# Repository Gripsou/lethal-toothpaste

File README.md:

README
======

BRIEF
-----

This is the repository for STM32 sockets.

NOTE :
------

This text is in _Work in Progress_ state.

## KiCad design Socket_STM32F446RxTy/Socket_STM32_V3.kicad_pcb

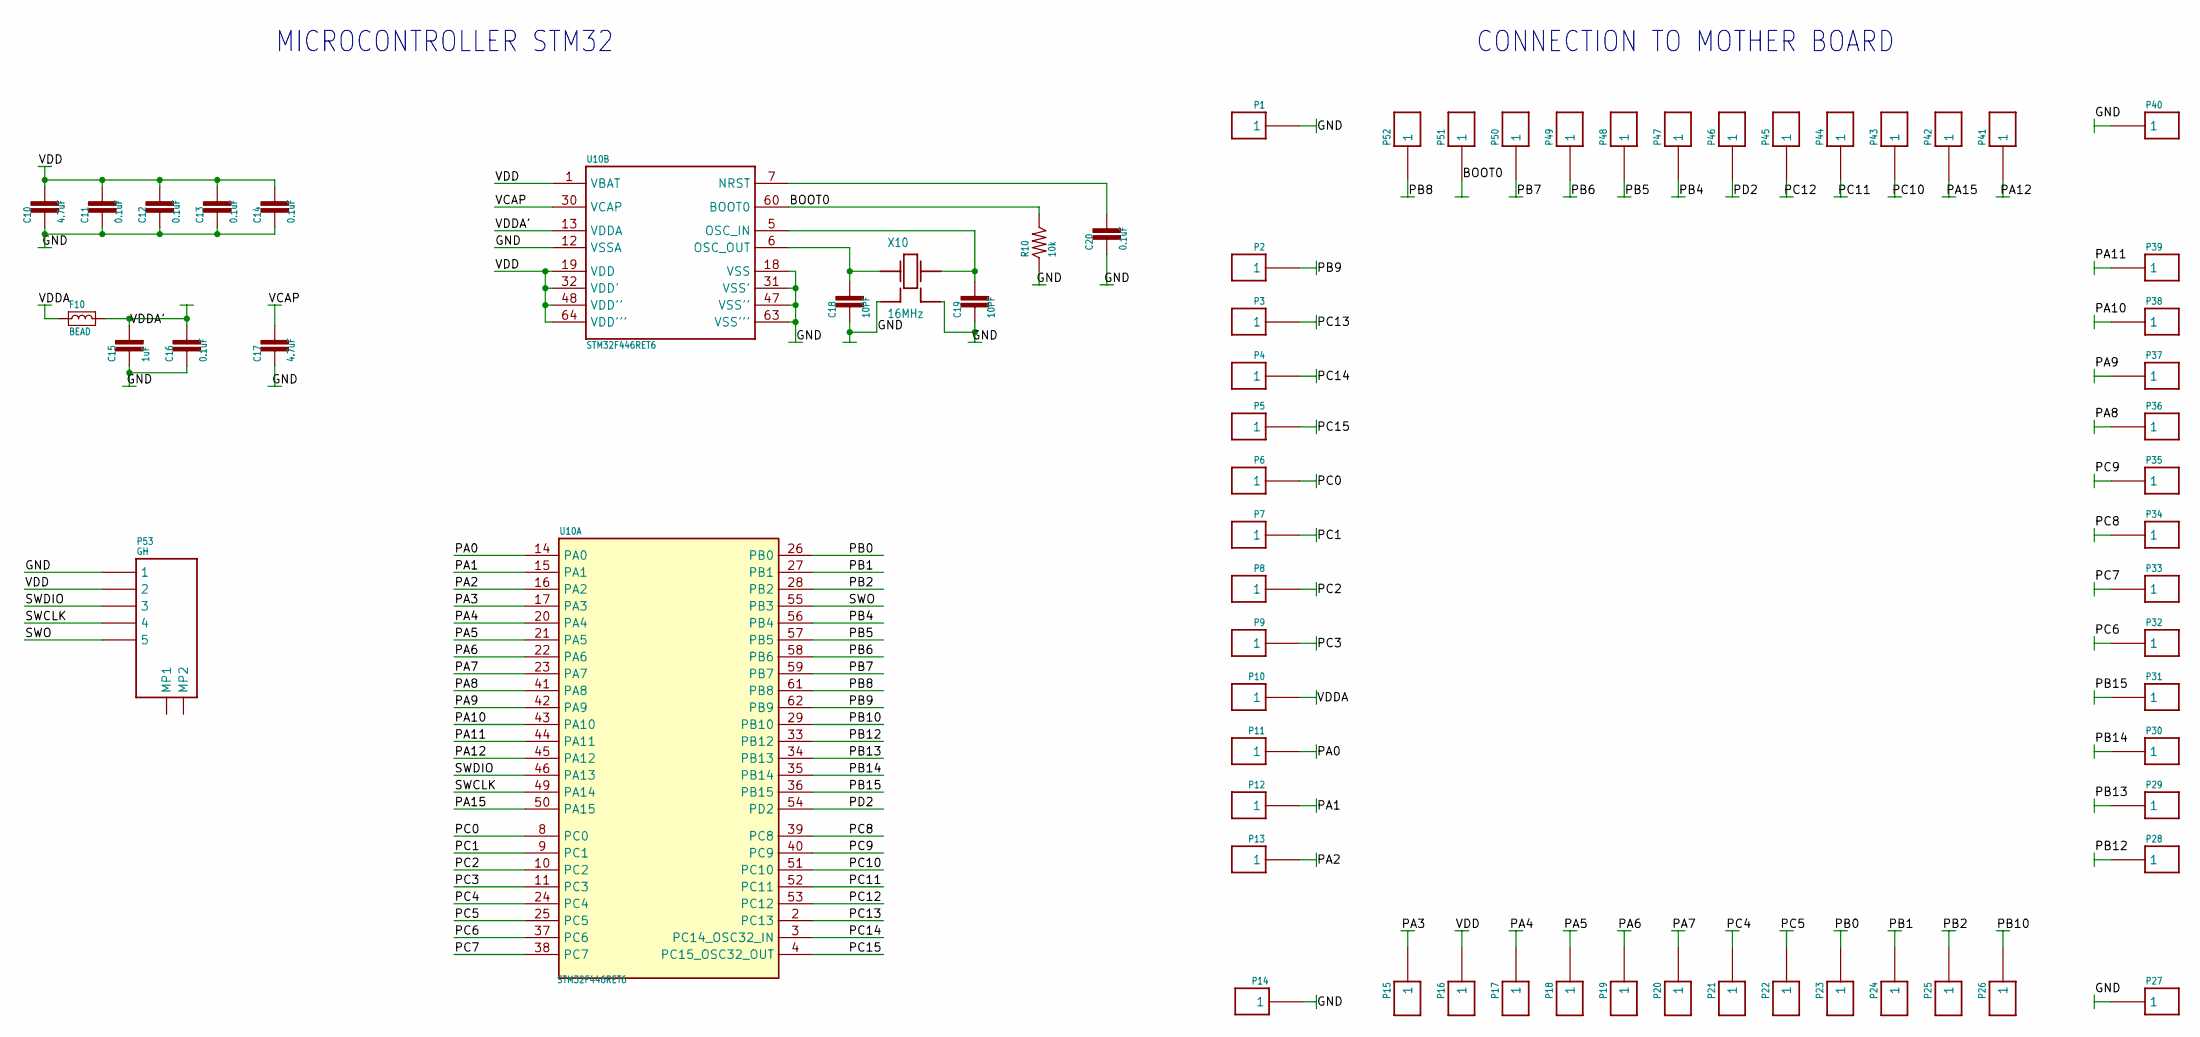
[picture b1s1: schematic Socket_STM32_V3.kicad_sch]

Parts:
C10, C17: 4.7uF; 0805_GRM
C11, C12, C13, C14, C16, C20: 0.1uF; 0805_GRM
C15: 1uF; 0805_GRM
C18, C19: 10PF; 0805_GRM
F10: BEAD; FERRITE_0805
P1, P14, P27, P40: PAD_CASTELLATED_HOLE_CORNER
P2, P3, P4, P5, P6, P7, P8, P9, P10, P11, P12, P13, P15, P16, P17, P18, P19, P20, P21, P22, P23, P24, P25, P26, P28, P29, P30, P31, P32, P33, P34, P35, P36, P37, P38, P39, P41, P42, P43, P44, P45, P46, P47, P48, P49, P50, P51, P52: PAD_1_1.51.2; PAD_1_1.5_1.2
P53: GH; JST_GH_5F
R10: 10k; RES_0805_ERJ
U10: STM32F446RET6; LQFP_64
X10: 16MHz; QUARTZ_TSX_3225

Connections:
BOOT0: P51.1, P51.2, P51.3, R10.2, U10.60 (BOOT0)
GND: C10.2 (1), C11.2 (1), C12.2 (1), C13.2 (1), C14.2 (1), C15.2 (1), C16.2 (1), C17.2 (1), C18.1, C19.1, C20.2 (1), P1.1, P14.1, P27.1, P40.1, P53.1, R10.1, U10.12 (VSSA), U10.18 (VSS), U10.31 (VSS'), U10.47 (VSS''), U10.63 (VSS'''), X10.2 (4), X10.4 (3)
unnamed: C18.2, U10.6 (OSC_OUT), X10.1
unnamed: C19.2, U10.5 (OSC_IN), X10.3 (2)
NRST: C20.1 (2), U10.7 (NRST)
PA0: P11.1, P11.2, P11.3, U10.14 (PA0)
PA1: P12.1, P12.2, P12.3, U10.15 (PA1)
PA2: P13.1, P13.2, P13.3, U10.16 (PA2)
PA3: P15.1, P15.2, P15.3, U10.17 (PA3)
PA4: P17.1, P17.2, P17.3, U10.20 (PA4)
PA5: P18.1, P18.2, P18.3, U10.21 (PA5)
PA6: P19.1, P19.2, P19.3, U10.22 (PA6)
PA7: P20.1, P20.2, P20.3, U10.23 (PA7)
PA8: P36.1, P36.2, P36.3, U10.41 (PA8)
PA9: P37.1, P37.2, P37.3, U10.42 (PA9)
PA10: P38.1, P38.2, P38.3, U10.43 (PA10)
PA11: P39.1, P39.2, P39.3, U10.44 (PA11)
PA12: P41.1, P41.2, P41.3, U10.45 (PA12)
PA15: P42.1, P42.2, P42.3, U10.50 (PA15)
PB0: P23.1, P23.2, P23.3, U10.26 (PB0)
PB1: P24.1, P24.2, P24.3, U10.27 (PB1)
PB2: P25.1, P25.2, P25.3, U10.28 (PB2)
PB4: P47.1, P47.2, P47.3, U10.56 (PB4)
PB5: P48.1, P48.2, P48.3, U10.57 (PB5)
PB6: P49.1, P49.2, P49.3, U10.58 (PB6)
PB7: P50.1, P50.2, P50.3, U10.59 (PB7)
PB8: P52.1, P52.2, P52.3, U10.61 (PB8)
PB9: P2.1, P2.2, P2.3, U10.62 (PB9)
PB10: P26.1, P26.2, P26.3, U10.29 (PB10)
PB12: P28.1, P28.2, P28.3, U10.33 (PB12)
PB13: P29.1, P29.2, P29.3, U10.34 (PB13)
PB14: P30.1, P30.2, P30.3, U10.35 (PB14)
PB15: P31.1, P31.2, P31.3, U10.36 (PB15)
PC0: P6.1, P6.2, P6.3, U10.8 (PC0)
PC1: P7.1, P7.2, P7.3, U10.9 (PC1)
PC2: P8.1, P8.2, P8.3, U10.10 (PC2)
PC3: P9.1, P9.2, P9.3, U10.11 (PC3)
PC4: P21.1, P21.2, P21.3, U10.24 (PC4)
PC5: P22.1, P22.2, P22.3, U10.25 (PC5)
PC6: P32.1, P32.2, P32.3, U10.37 (PC6)
PC7: P33.1, P33.2, P33.3, U10.38 (PC7)
PC8: P34.1, P34.2, P34.3, U10.39 (PC8)
PC9: P35.1, P35.2, P35.3, U10.40 (PC9)
PC10: P43.1, P43.2, P43.3, U10.51 (PC10)
PC11: P44.1, P44.2, P44.3, U10.52 (PC11)
PC12: P45.1, P45.2, P45.3, U10.53 (PC12)
PC13: P3.1, P3.2, P3.3, U10.2 (PC13)
PC14: P4.1, P4.2, P4.3, U10.3 (PC14_OSC32_IN)
PC15: P5.1, P5.2, P5.3, U10.4 (PC15_OSC32_OUT)
PD2: P46.1, P46.2, P46.3, U10.54 (PD2)
SWCLK: P53.4, U10.49 (PA14)
SWDIO: P53.3, U10.46 (PA13)
SWO: P53.5, U10.55 (PB3)
VCAP: C17.1 (2), U10.30 (VCAP)
VDD: C10.1 (2), C11.1 (2), C12.1 (2), C13.1 (2), C14.1 (2), P16.1, P16.2, P16.3, P53.2, U10.1 (VBAT), U10.19 (VDD), U10.32 (VDD'), U10.48 (VDD''), U10.64 (VDD''')
VDDA: F10.1, P10.1, P10.2, P10.3
VDDA': C15.1 (2), C16.1 (2), F10.2, U10.13 (VDDA)

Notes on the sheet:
CONNECTION TO MOTHER BOARD
MICROCONTROLLER STM32

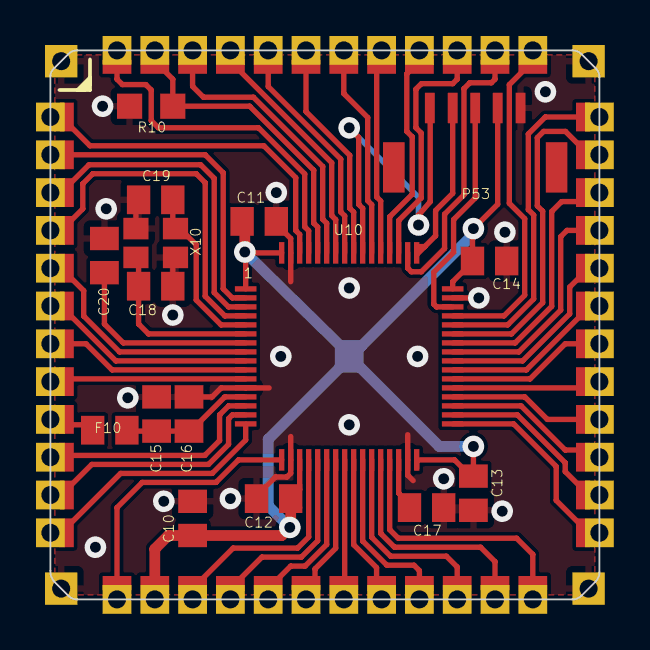
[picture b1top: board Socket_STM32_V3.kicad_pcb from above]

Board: 2 copper layers, 30.5 x 30.5 mm, 68 parts (0 on the bottom side), 57 nets.

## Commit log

2024-12-09 Initial Commit
    * Create repository
    * Create `README.md` file
2025-01-16 Add .gitignore
    Add ".gitignore" file in order to avoid commiting temporary and backup files.
2025-01-16 Import STM32F446RxTy EAGLE project
    Import EAGLE project for STM32F446RxTy microcontroller. It will be valid for STM32F446RET6, STM32F446RET7 and STM32F446RCT6, STM32F446RCT7.
2025-01-16 Update 3D models
    Update 3D models for footprint in local library. 3D model used are KiCad 8 standard library ones.
    NOTES :
    - Ferrite 3D model has to be updated since we use the 0805 resistor at the moment.
    - Update Crystal 3D model. This one is not updated in design so far.
2025-01-16 Update STM32F446 symbol
    * Create 0,25mm gird and set project on this new one
    * Update STM32F446RET6 symbol in local library.
    * Update schematic from local library
    * Remove empty sheet background.
2025-01-16 Update Ferrite 3D model
    * Import Ferrite 3D model to repository : package is 0805.
    * Update component in local component footprint library (".kicad_mod" file).
    * Perform componen update from library in PCB layout.
2025-01-16 Update footprints
    Update silkscreen size so they are fraction of metric dimensions
2025-01-16 Update quartz footprint & 3D model
    * Add 3D model to footprint
    * Update silkscreen size
2025-01-16 Update PCB layout
    Update PCB layout (and 3D model) from updated footprint libraries.
2025-01-16 Update symbols & schematic
    * Improve symbols in library
    * Update all symbols in schematic from library
2025-01-16 Export 3D model
    Export 3D model in VRML and STEP file format.
